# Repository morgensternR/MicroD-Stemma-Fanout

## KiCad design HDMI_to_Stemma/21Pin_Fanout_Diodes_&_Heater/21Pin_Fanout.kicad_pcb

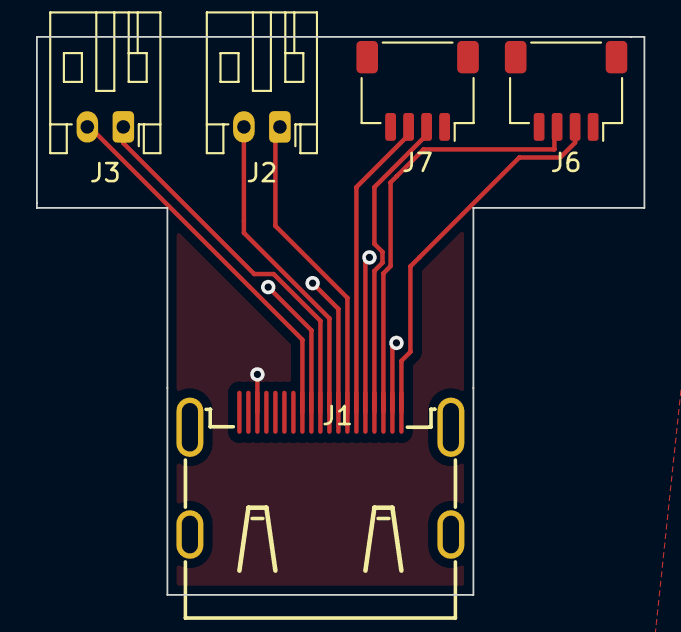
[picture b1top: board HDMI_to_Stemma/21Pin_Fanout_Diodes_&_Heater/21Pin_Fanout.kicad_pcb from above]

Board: 2 copper layers, 33.8 x 31.0 mm, 5 parts (0 on the bottom side), 9 nets.

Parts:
J1: HDMI_A; HDMI-SMD_HDMI-019S
J2, J3: Conn_01x02; JST_PH_S2B-PH-K_1x02_P2.00mm_Horizontal
J6, J7: Conn_01x04; JST_SH_SM04B-SRSS-TB_1x04-1MP_P1.00mm_Horizontal

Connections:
GND: J1.2 (D2S), J1.5 (D1S), J1.8 (D0S), J1.11 (CKS), J1.17 (GND)
unnamed: J1.1 (D2+), J6.2
unnamed: J1.3 (D2-), J6.3
unnamed: J1.4 (D1+), J7.2
unnamed: J1.6 (D1-), J7.3
unnamed: J1.7 (D0+), J2.1
unnamed: J1.9 (D0-), J2.2
unnamed: J1.10 (CK+), J3.1
unnamed: J1.12 (CK-), J3.2

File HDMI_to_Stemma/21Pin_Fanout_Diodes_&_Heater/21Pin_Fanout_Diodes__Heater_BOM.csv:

Comment,Designator,Footprint,LCSC
"HDMI_A","J1","0_21Pin_FootprintLib:HDMI-SMD_HDMI-019S","C111617"
"Conn_01x02","J2,J3","Connector_JST:JST_PH_S2B-PH-K_1x02_P2.00mm_Horizontal","C16965"
"Conn_01x04","J6,J7","Connector_JST:JST_SH_SM04B-SRSS-TB_1x04-1MP_P1.00mm_Horizontal","C371571"

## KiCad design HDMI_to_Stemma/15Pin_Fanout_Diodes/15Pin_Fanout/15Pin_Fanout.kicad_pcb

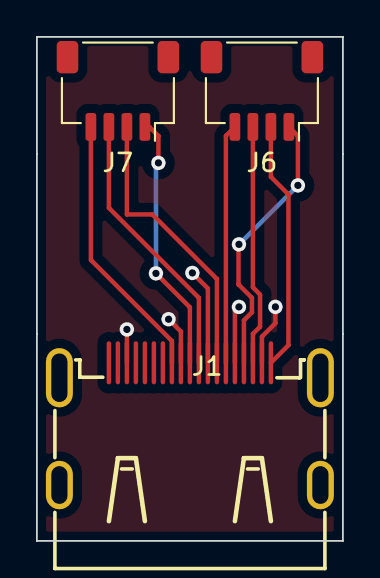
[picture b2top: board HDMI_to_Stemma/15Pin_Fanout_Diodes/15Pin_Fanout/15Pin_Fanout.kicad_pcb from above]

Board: 2 copper layers, 17.0 x 28.0 mm, 3 parts (0 on the bottom side), 9 nets.

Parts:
J1: HDMI_A; HDMI-SMD_HDMI-019S
J6, J7: Conn_01x04; JST_SH_SM04B-SRSS-TB_1x04-1MP_P1.00mm_Horizontal

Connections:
GND: J1.2 (D2S), J1.5 (D1S), J1.8 (D0S), J1.11 (CKS), J1.17 (GND)
unnamed: J1.1 (D2+), J6.2
unnamed: J1.3 (D2-), J6.3
unnamed: J1.4 (D1+), J6.1
unnamed: J1.6 (D1-), J6.4
unnamed: J1.7 (D0+), J7.2
unnamed: J1.9 (D0-), J7.3
unnamed: J1.10 (CK+), J7.1
unnamed: J1.12 (CK-), J7.4

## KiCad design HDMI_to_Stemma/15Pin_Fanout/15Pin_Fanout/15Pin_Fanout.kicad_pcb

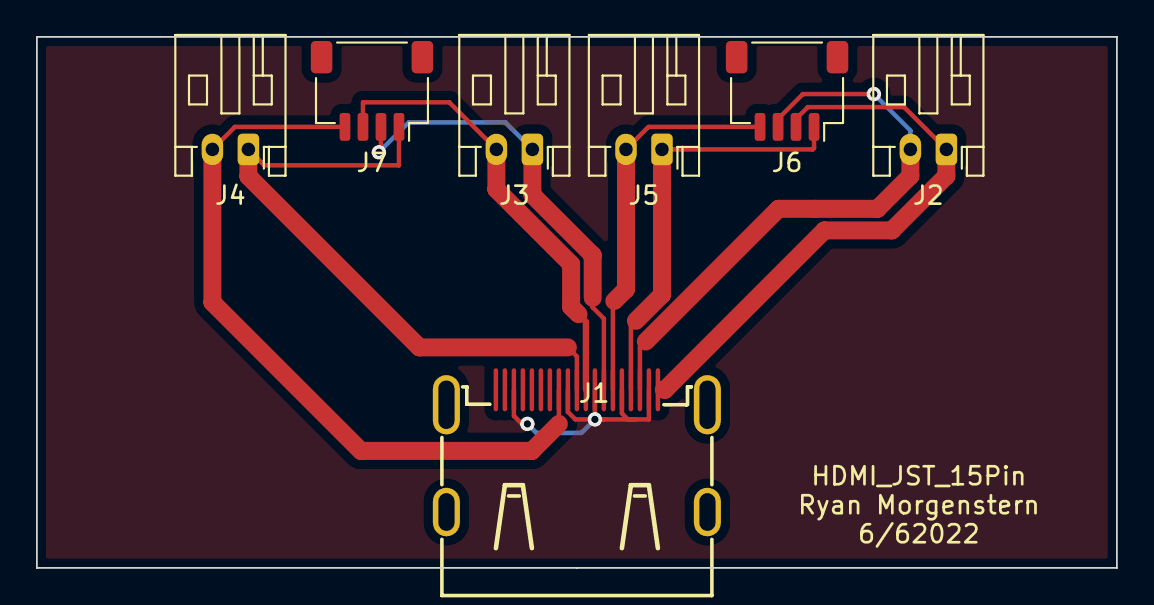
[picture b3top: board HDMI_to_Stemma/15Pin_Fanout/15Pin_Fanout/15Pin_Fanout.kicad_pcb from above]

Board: 2 copper layers, 60.0 x 29.5 mm, 7 parts (0 on the bottom side), 9 nets.

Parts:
J1: HDMI_A; HDMI-SMD_HDMI-019S
J2, J3, J4, J5: Conn_01x02; JST_PH_S2B-PH-K_1x02_P2.00mm_Horizontal
J6, J7: Conn_01x04; JST_SH_SM04B-SRSS-TB_1x04-1MP_P1.00mm_Horizontal

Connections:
GND: J1.2 (D2S), J1.5 (D1S), J1.8 (D0S), J1.11 (CKS), J1.17 (GND)
unnamed: J1.1 (D2+), J2.1, J6.2
unnamed: J1.3 (D2-), J2.2, J6.3
unnamed: J1.4 (D1+), J5.1, J6.1
unnamed: J1.6 (D1-), J5.2, J6.4
unnamed: J1.7 (D0+), J3.1, J7.2
unnamed: J1.9 (D0-), J3.2, J7.3
unnamed: J1.10 (CK+), J4.1, J7.1
unnamed: J1.12 (CK-), J4.2, J7.4

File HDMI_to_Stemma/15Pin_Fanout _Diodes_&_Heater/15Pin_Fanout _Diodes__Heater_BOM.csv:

Comment,Designator,Footprint,LCSC
HDMI_A,J1,0_15Pin_FootprintsLib:HDMI-SMD_HDMI-019S,C111617
Conn_01x04,J6,Connector_JST:JST_SH_SM04B-SRSS-TB_1x04-1MP_P1.00mm_Horizontal,C371571
Conn_01x02,"J2, J3",Connector_JST:JST_PH_S2B-PH-K_1x02_P2.00mm_Horizontal,C16965

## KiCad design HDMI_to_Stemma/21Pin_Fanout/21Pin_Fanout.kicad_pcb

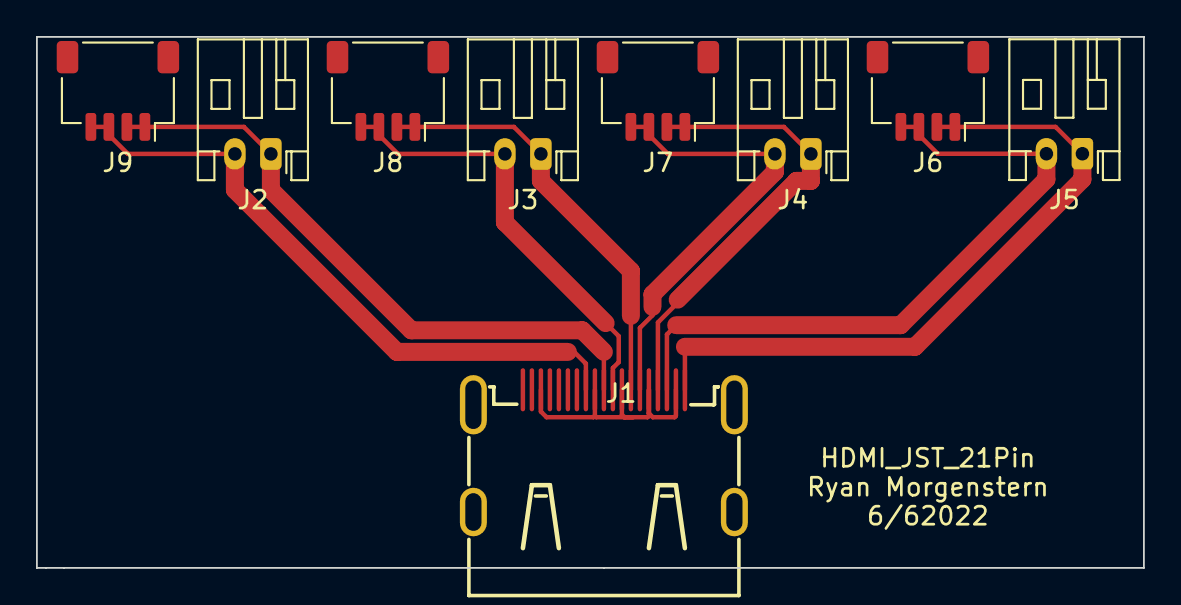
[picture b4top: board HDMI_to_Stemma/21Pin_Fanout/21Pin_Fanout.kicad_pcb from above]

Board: 2 copper layers, 61.5 x 29.5 mm, 9 parts (0 on the bottom side), 9 nets.

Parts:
J1: HDMI_A; HDMI-SMD_HDMI-019S
J2, J3, J4, J5: Conn_01x02; JST_PH_S2B-PH-K_1x02_P2.00mm_Horizontal
J6, J7, J8, J9: Conn_01x04; JST_SH_SM04B-SRSS-TB_1x04-1MP_P1.00mm_Horizontal

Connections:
GND: J1.2 (D2S), J1.5 (D1S), J1.8 (D0S), J1.11 (CKS), J1.17 (GND)
unnamed: J1.1 (D2+), J5.1, J6.1, J6.2
unnamed: J1.3 (D2-), J5.2, J6.3, J6.4
unnamed: J1.4 (D1+), J4.1, J7.1, J7.2
unnamed: J1.6 (D1-), J4.2, J7.3, J7.4
unnamed: J1.7 (D0+), J3.1, J8.1, J8.2
unnamed: J1.9 (D0-), J3.2, J8.3, J8.4
unnamed: J1.10 (CK+), J2.1, J9.1, J9.2
unnamed: J1.12 (CK-), J2.2, J9.3, J9.4

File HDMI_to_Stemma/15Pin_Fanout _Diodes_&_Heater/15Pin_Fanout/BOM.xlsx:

Comment | Designator | Footprint | LCSC
HDMI_A | J1 | 0_15Pin_FootprintsLib:HDMI-SMD_HDMI-019S | C111617
Conn_01x04 | J6 | Connector_JST:JST_SH_SM04B-SRSS-TB_1x04-1MP_P1.00mm_Horizontal | C371571
Conn_01x02 | J2, J3 | Connector_JST:JST_PH_S2B-PH-K_1x02_P2.00mm_Horizontal | C16965

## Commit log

2022-06-06 Added separate HDMI to stemma for 21 and 15 pin
2022-06-07 Updated traces
2022-06-22 Updated names
